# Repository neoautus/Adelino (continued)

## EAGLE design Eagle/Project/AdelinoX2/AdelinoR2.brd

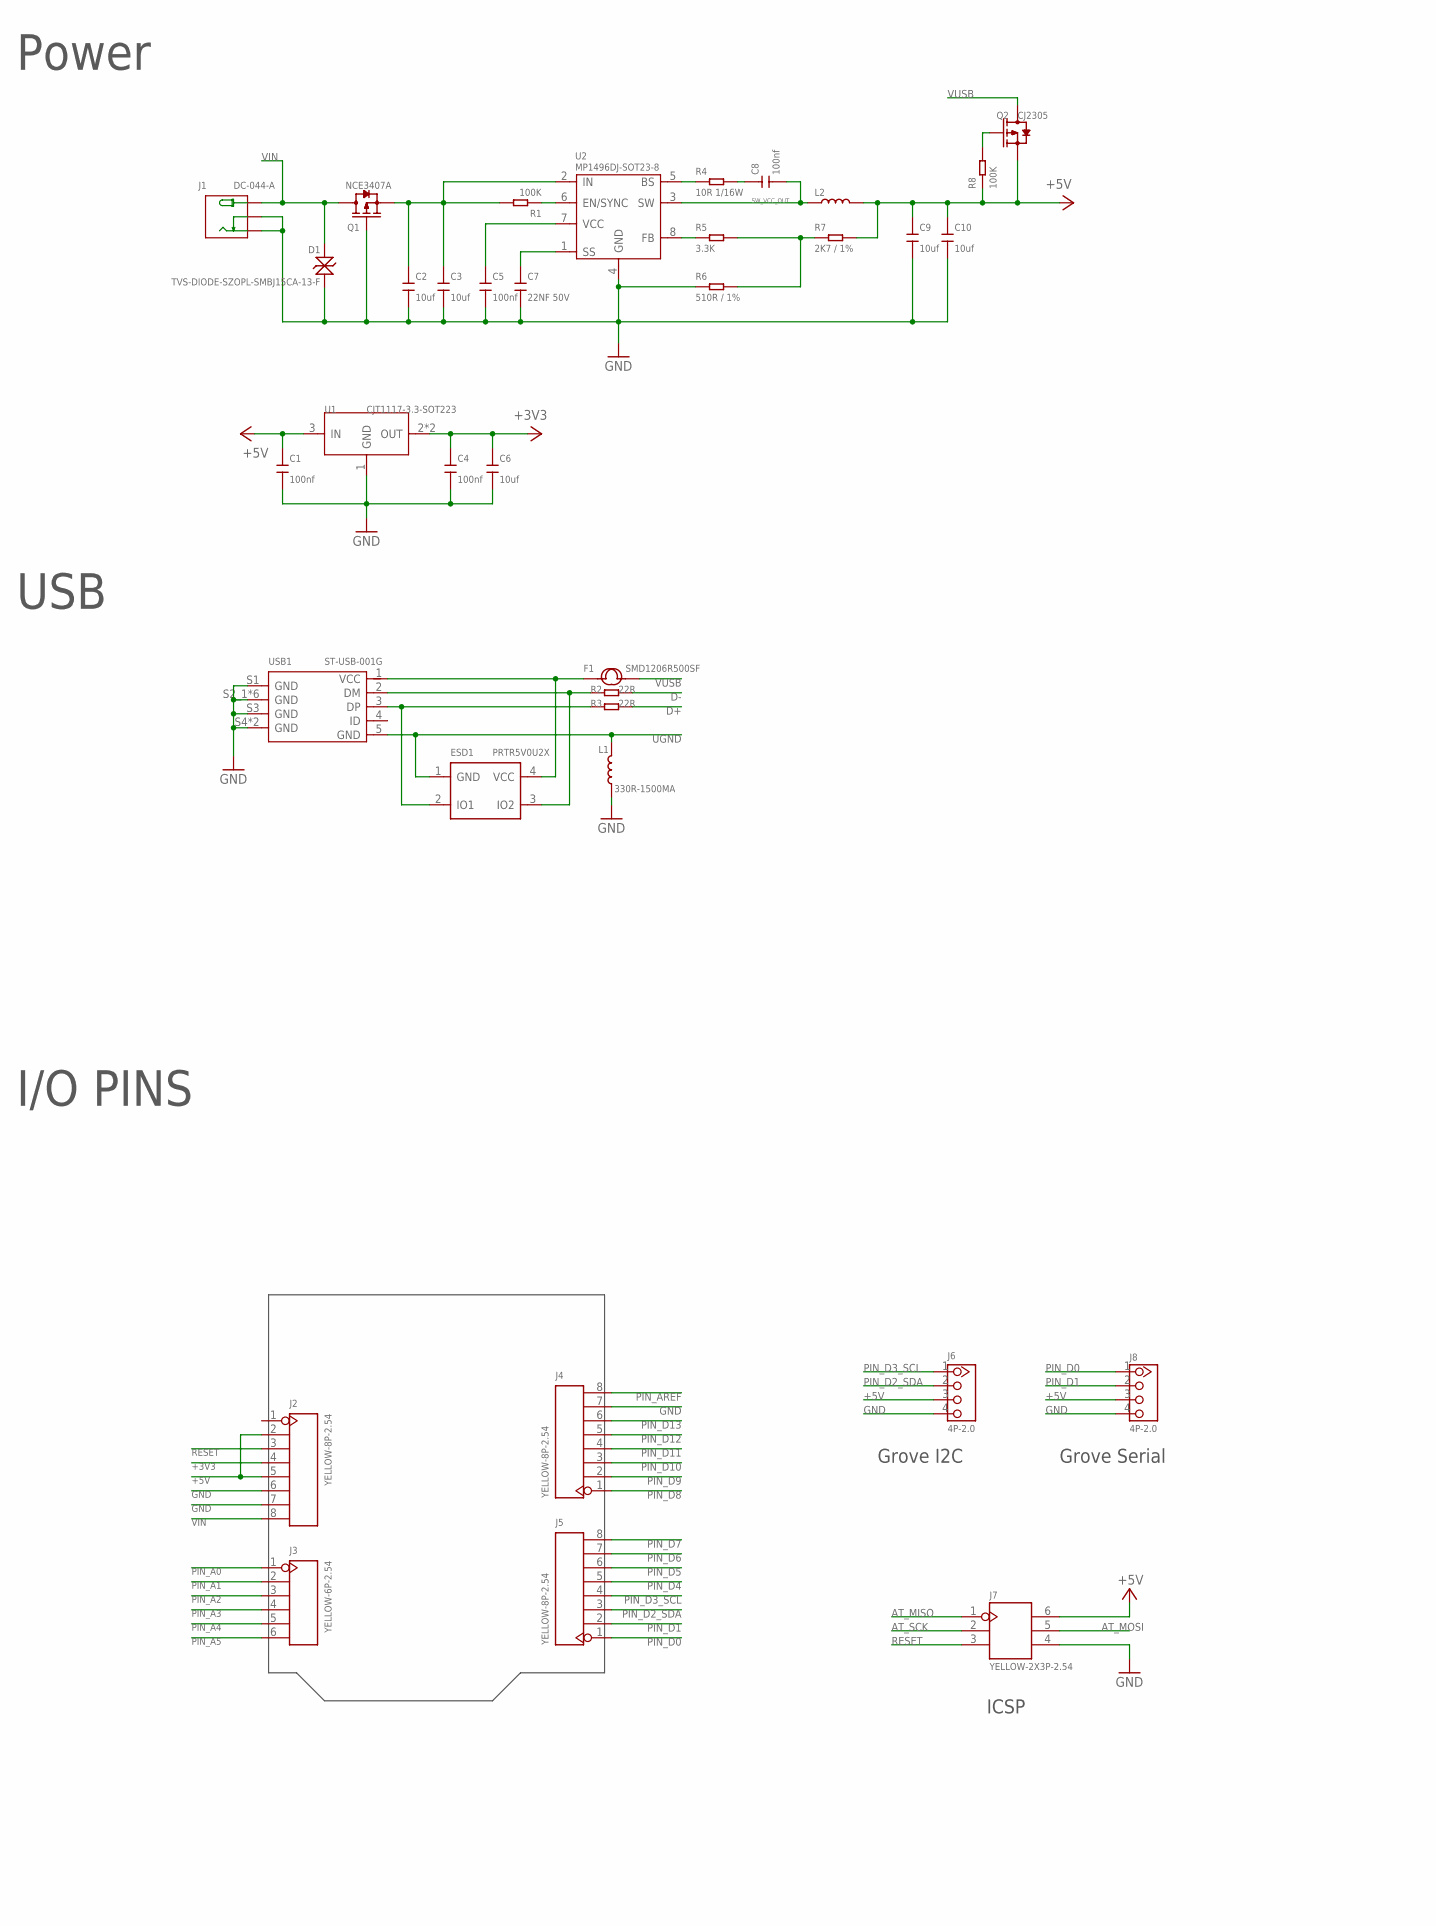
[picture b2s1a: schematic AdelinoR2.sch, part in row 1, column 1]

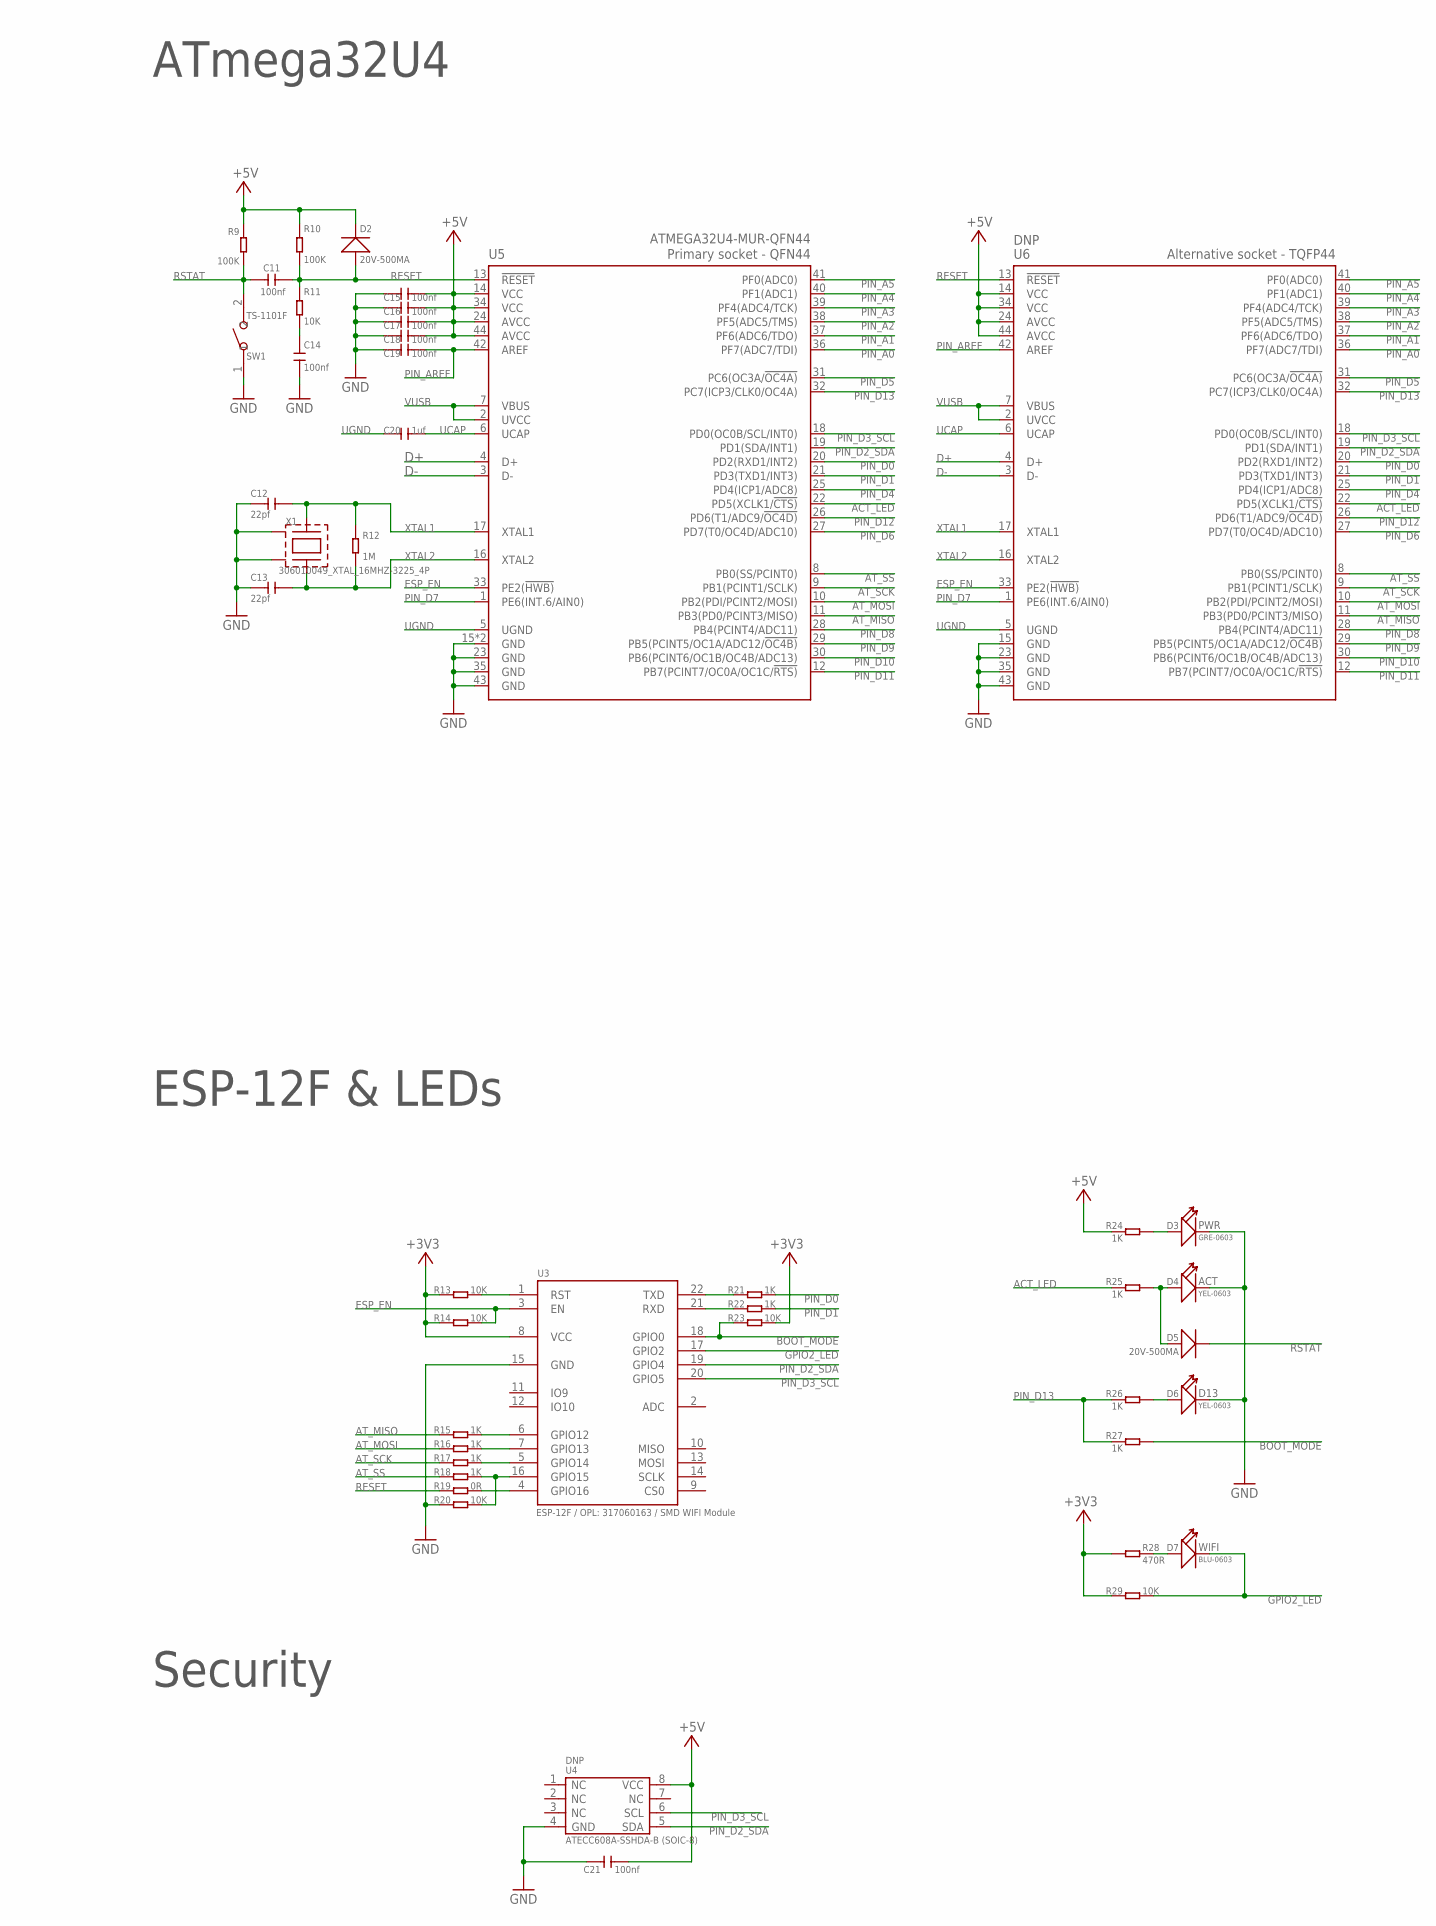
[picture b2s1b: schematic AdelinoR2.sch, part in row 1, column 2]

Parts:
C1, C4, C5, C8, C11, C14, C15, C16, C17, C18, C19, C21: 100nf; C0402
C2, C3, C6, C9, C10: 10uf; C0805
C7: 22NF 50V; C0402
C12, C13: 22pf; C0402
C20: 1uf; C0805
D1: TVS-DIODE-SZOPL-SMBJ15CA-13-F; DO-214AA
D2, D5: 20V-500MA; SOD-123
D3: GRE-0603; LED-0603
D4, D6: YEL-0603; LED-0603
D7: BLU-0603; LED-0603
ESD1: PRTR5V0U2X; SOT-143B
F1: SMD1206R500SF; F1206
J1: DC-044-A; DCJ3P-11.6X9.6X7.0MM
J2, J4, J5: YELLOW-8P-2.54; H8-2.54
J3: YELLOW-6P-2.54; H6-2.54
J6, J8: 4P-2.0; HW4-2.0
J7: YELLOW-2X3P-2.54; H2X3-2.54
L1: 330R-1500MA; L0805
L2: 10UH-225MA; L5040S
Q1: NCE3407A; SOT-23
Q2: CJ2305; SOT-23
R1, R8, R9, R10: 100K; R0402
R2, R3: 22R; R0402
R4: 10R 1/16W; R0402
R5: 3.3K; R0402
R6: 3K / 1%; R0603
R7: 2K7 / 1%; R0603
R11, R13, R14, R20, R23, R29: 10K; R0402
R12: 1M; R0402
R15, R16, R17, R18, R21, R22, R24, R25, R26, R27: 1K; R0402
R19: 0R; R0402
R28: 470R; R0402
SW1: TS-1101F; SW2-5.0-6.0X3.0X4.3MM
U1: CJT1117-3.3-SOT223; SOT-223
U2: MP1496DJ-SOT23-8; SOT-23-8
U3: ESP-12F / OPL: 317060163 / SMD WIFI Module; ESP-12F
U4: DNP; SOIC8-1.27-5X4MM; MPN ATECC608A-SSHDA-B
U5: ATMEGA32U4-MUR-QFN44; QFN44G-0.5-7X7MM
U6: DNP; TQFP44-0.8-9.6X9.6MM
USB1: ST-USB-001G; MICRO-USB5+4P-SMD-0.65-B
X1: 306010049_XTAL_16MHZ-3225_4P; X3225_4P

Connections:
+3V3: C4.2, C6.2, J2.4, R13.1, R14.1, R23.2, R28.1, R29.1, U1.2 (OUT), U1.TER (OUT), U3.8 (VCC)
+5V: C1.2, C9.2, C10.2, C15.1, C16.1, C17.1, C18.1, C21.1, D2.-, J2.2, J2.5, J6.3, J7.6, J8.3, L2.2, Q2.2 (S), R7.2, R8.1, R9.1, R10.2, R24.1, U1.3 (IN), U4.8 (VCC), U5.14 (VCC), U5.24 (AVCC), U5.34 (VCC), U5.44 (AVCC), U6.14 (VCC), U6.24 (AVCC), U6.34 (VCC), U6.44 (AVCC)
ACT_LED: R25.1, U5.22 (PD5(XCLK1/!CTS)), U6.22 (PD5(XCLK1/!CTS))
AT_MISO: J7.1, R15.1, U5.11 (PB3(PD0/PCINT3/MISO)), U6.11 (PB3(PD0/PCINT3/MISO))
AT_MOSI: J7.5, R16.1, U5.10 (PB2(PDI/PCINT2/MOSI)), U6.10 (PB2(PDI/PCINT2/MOSI))
AT_SCK: J7.2, R17.1, U5.9 (PB1(PCINT1/SCLK)), U6.9 (PB1(PCINT1/SCLK))
AT_SS: R18.1, U5.8 (PB0(SS/PCINT0)), U6.8 (PB0(SS/PCINT0))
BOOT_MODE: R23.1, R27.2, U3.18 (GPIO0)
D+: R3.2, U5.4 (D+), U6.4 (D+)
D-: R2.2, U5.3 (D-), U6.3 (D-)
ESP_EN: R14.2, U3.3 (EN), U5.33 (PE2(!HWB)), U6.33 (PE2(!HWB))
GND: C1.1, C2.1, C3.1, C4.1, C5.1, C6.1, C7.1, C9.1, C10.1, C12.1, C13.1, C14.2, C15.2, C16.2, C17.2, C18.2, C19.2, C21.2, D1.+, D3.-, D4.-, D6.-, J1.CDN1 (CDN), J1.CDN2 (CDN), J1.CDN3 (CDN), J1.CDN4 (CDN), J1.GND1 (-), J1.GND2 (-), J1.GND3 (-), J1.GND4 (-), J2.6, J2.7, J4.7, J6.4, J7.4, J8.4, L1.1, Q1.1 (G), R6.1, R20.1, SW1.1, U1.1 (GND), U2.4 (GND), U3.15 (GND), U4.4 (GND), U5.15 (GND), U5.23 (GND), U5.35 (GND), U5.43 (GND), U5.TAB (GND), U6.15 (GND), U6.23 (GND), U6.35 (GND), U6.43 (GND), USB1.S1 (GND), USB1.S2_1 (GND), USB1.S2_2 (GND), USB1.S2_3 (GND), USB1.S3 (GND), USB1.S4 (GND), USB1.S5_1 (GND), USB1.S5_2 (GND), USB1.S5_3 (GND), USB1.S6 (GND), X1.P$2 (GND1), X1.P$4 (GND2)
GPIO2_LED: D7.-, R29.2, U3.17 (GPIO2)
unnamed: ESD1.3 (IO2), R2.1, USB1.2 (DM)
unnamed: ESD1.2 (IO1), R3.1, USB1.3 (DP)
unnamed: Q2.1 (G), R8.2
unnamed: D7.+, R28.2
unnamed: R19.2, U3.4 (GPIO16)
unnamed: ESD1.4 (VCC), F1.1, USB1.1 (VCC)
unnamed: R15.2, U3.6 (GPIO12)
unnamed: C14.1, R11.2
unnamed: R16.2, U3.7 (GPIO13)
unnamed: C8.2, R4.2
unnamed: R21.1, U3.22 (TXD)
unnamed: R22.1, U3.21 (RXD)
unnamed: R17.2, U3.5 (GPIO14)
unnamed: R18.2, R20.2, U3.16 (GPIO15)
unnamed: R13.2, U3.1 (RST)
unnamed: R5.2, R6.2, R7.1
PIN_A0: J3.1, U5.36 (PF7(ADC7/TDI)), U6.36 (PF7(ADC7/TDI))
PIN_A1: J3.2, U5.37 (PF6(ADC6/TDO)), U6.37 (PF6(ADC6/TDO))
PIN_A2: J3.3, U5.38 (PF5(ADC5/TMS)), U6.38 (PF5(ADC5/TMS))
PIN_A3: J3.4, U5.39 (PF4(ADC4/TCK)), U6.39 (PF4(ADC4/TCK))
PIN_A4: J3.5, U5.40 (PF1(ADC1)), U6.40 (PF1(ADC1))
PIN_A5: J3.6, U5.41 (PF0(ADC0)), U6.41 (PF0(ADC0))
PIN_AREF: C19.1, J4.8, U5.42 (AREF), U6.42 (AREF)
PIN_D0: J5.1, J8.1, R21.2, U5.20 (PD2(RXD1/INT2)), U6.20 (PD2(RXD1/INT2))
PIN_D1: J5.2, J8.2, R22.2, U5.21 (PD3(TXD1/INT3)), U6.21 (PD3(TXD1/INT3))
PIN_D2_SDA: J5.3, J6.2, U3.19 (GPIO4), U4.5 (SDA), U5.19 (PD1(SDA/INT1)), U6.19 (PD1(SDA/INT1))
PIN_D3_SCL: J5.4, J6.1, U3.20 (GPIO5), U4.6 (SCL), U5.18 (PD0(OC0B/SCL/INT0)), U6.18 (PD0(OC0B/SCL/INT0))
PIN_D4: J5.5, U5.25 (PD4(ICP1/ADC8)), U6.25 (PD4(ICP1/ADC8))
PIN_D5: J5.6, U5.31 (PC6(OC3A/!OC4A)), U6.31 (PC6(OC3A/!OC4A))
PIN_D6: J5.7, U5.27 (PD7(T0/OC4D/ADC10)), U6.27 (PD7(T0/OC4D/ADC10))
PIN_D7: J5.8, U5.1 (PE6(INT.6/AIN0)), U6.1 (PE6(INT.6/AIN0))
PIN_D8: J4.1, U5.28 (PB4(PCINT4/ADC11)), U6.28 (PB4(PCINT4/ADC11))
PIN_D9: J4.2, U5.29 (PB5(PCINT5/OC1A/ADC12/!OC4B)), U6.29 (PB5(PCINT5/OC1A/ADC12/!OC4B))
PIN_D10: J4.3, U5.30 (PB6(PCINT6/OC1B/OC4B/ADC13)), U6.30 (PB6(PCINT6/OC1B/OC4B/ADC13))
PIN_D11: J4.4, U5.12 (PB7(PCINT7/OC0A/OC1C/!RTS)), U6.12 (PB7(PCINT7/OC0A/OC1C/!RTS))
PIN_D12: J4.5, U5.26 (PD6(T1/ADC9/!OC4D)), U6.26 (PD6(T1/ADC9/!OC4D))
PIN_D13: J4.6, R26.1, R27.1, U5.32 (PC7(ICP3/CLK0/OC4A)), U6.32 (PC7(ICP3/CLK0/OC4A))
RESET: C11.1, D2.+, J2.3, J7.3, R10.1, R11.1, R19.1, U5.13 (!RESET), U6.13 (!RESET)
RSTAT: C11.2, D5.-, R9.2, SW1.2
SW_BS: R4.1, U2.5 (BS)
SW_EN: R1.1, U2.6 (EN/SYNC)
SW_FB: R5.1, U2.8 (FB)
SW_SS: C7.2, U2.1 (SS)
SW_VCAP: C5.2, U2.7 (VCC)
SW_VCC_IN: C2.2, C3.2, Q1.2 (S), R1.2, U2.2 (IN)
SW_VCC_OUT: C8.1, L2.1, U2.3 (SW)
UCAP: C20.2, U5.6 (UCAP), U6.6 (UCAP)
UGND: C20.1, ESD1.1 (GND), L1.2, U5.5 (UGND), U6.5 (UGND), USB1.5 (GND)
VIN: D1.-, J1.VCC1 (+), J1.VCC2 (+), J1.VCC3 (+), J1.VCC4 (+), J2.8, Q1.3 (D)
VUSB: F1.2, Q2.3 (D), U5.2 (UVCC), U5.7 (VBUS), U6.2 (UVCC), U6.7 (VBUS)
XTAL1: C12.2, R12.2, U5.17 (XTAL1), U6.17 (XTAL1), X1.P$1
XTAL2: C13.2, R12.1, U5.16 (XTAL2), U6.16 (XTAL2), X1.P$3
_ACT: D4.+, D5.+, R25.2
_D13: D6.+, R26.2
_PWR: D3.+, R24.2

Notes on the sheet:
USB
Power
ATmega32U4
ESP-12F & LEDs
I/O PINS
Grove I2C
Grove Serial
Security
ICSP

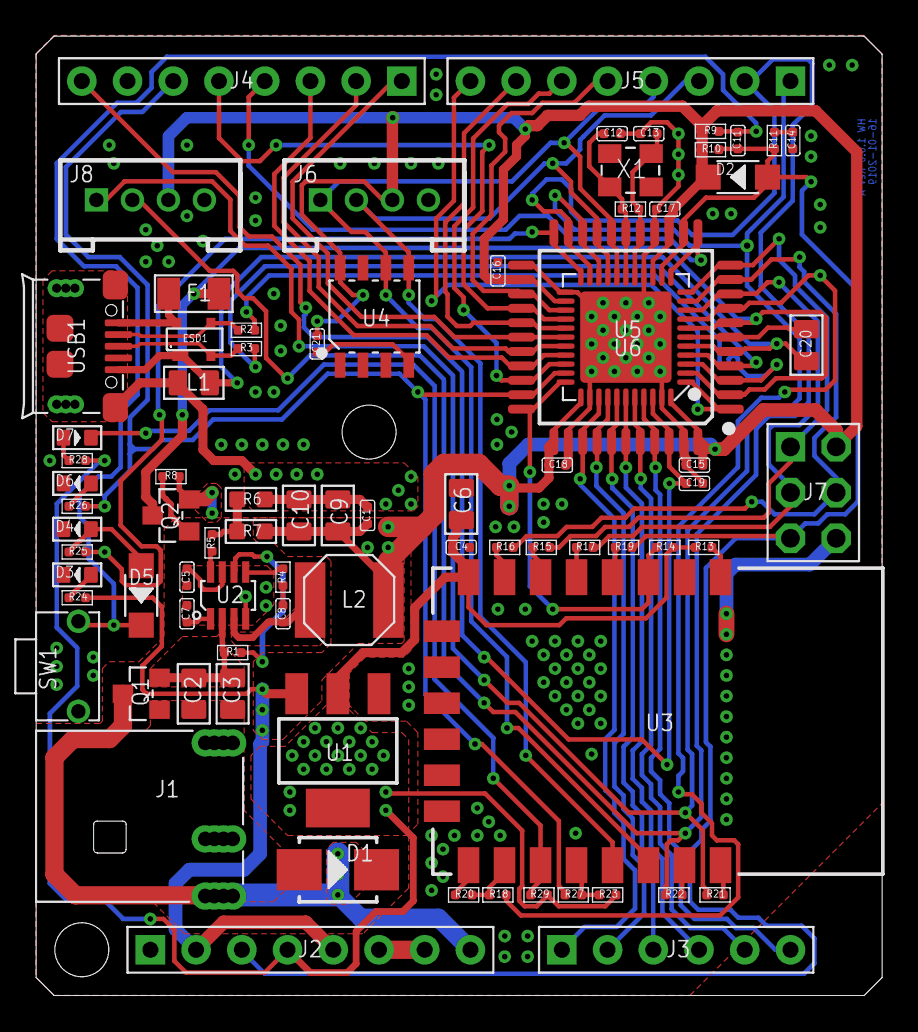
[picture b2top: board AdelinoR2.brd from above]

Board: 2 copper layers, 47.0 x 53.3 mm, 80 parts (0 on the bottom side), 68 nets.

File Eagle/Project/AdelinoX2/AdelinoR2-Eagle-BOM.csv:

"Parts";"Qty";"Value";"Device";"Package";"OPL";"MPN";"DESC"
"R19";1;"0R";"SMD-RES-0R-5%-1/16W(0402)";"R0402";301010000;"RC0402JR-070RL";"0R"
"R1, R8, R9, R10";4;"100K";"SMD-RES-100K-1%-1/16W(0402)";"R0402";301010456;"RC0402FR-07100KL";"100K"
"C1, C4, C5, C8, C11, C14, C15, C16, C17, C18, C19, C21";12;"100nf";"CERAMIC-100NF-25V-10%-X7R(0402)";"C0402";302010024;"CC0402KRX7R8BB104";"100nf"
"R11, R13, R14, R20, R23, R29";6;"10K";"SMD-RES-10K-1%-1/16W(0402)";"R0402";301010047;"RC0402FR-0710KL";"10K 1/16W"
"R4";1;"10R 1/16W";"SMD-RES-10R-1%-1/16W(0402)";"R0402";301010444;"RC0402FR-0710RL";"10R 1/16W"
"L2";1;"10UH-225MA";"SMD-INDUCTOR-10UH-20%-2.35A(2P-5X5X4MM)";"L5040S";303010147;;"SMD-INDUCTOR-10UH-20%-2.35A(2P-5X5X4MM)"
"C2, C3, C6, C9, C10";5;"10uf";"CERAMIC-10UF-25V-10%-X5R(0805)";"C0805";302010178;"CC0805KKX5R8BB106";"10uf"
"R15, R16, R17, R18, R21, R22, R24, R25, R26, R27";10;"1K";"SMD-RES-1K-5%-1/16W(0402)";"R0402";301010006;"RC0402JR-071KL";"1K"
"R12";1;"1M";"SMD-RES-1M-1%-1/16W(0402)";"R0402";301010043;"RC0402FR-071ML";"1M"
"C20";1;"1uf";"CERAMIC-1UF-25V-10%-X7R(0805)";"C0805";302010179;"CC0805KKX7R8BB105";"1uf"
"D2, D5";2;"20V-500MA";"SMD-DIODE-SCHOTTKY-20V-500MA(SOD-123)P";"SOD-123";304020028;"MBR0520LT1G";"20V-500MA"
"C7";1;"22NF 50V";"CERAMIC-22NF-50V-10%-X7R(0402)";"C0402";302010242;"CC0402KRX7R9BB223";"22NF 50V"
"R2, R3";2;"22R";"SMD-RES-22R-1%-1/16W(0402)";"R0402";301010052;"RC0402FR-0722RL";"22R"
"C12, C13";2;"22pf";"CERAMIC-22PF-50V-5%-NPO(0402)";"C0402";302010018;"CC0402JRNPO9BN220";"22pf"
"R7";1;"2K7 / 1%";"SMD-RES-2.7K-1%-1/10W(0603)";"R0603";301010193;;"2K7 / 1%"
"R5";1;"3.3K";"SMD-RES-3.3K-5%-1/16W(0402)";"R0402";301010035;"RC0402JR-073K3L";"3.3K"
"X1";1;"306010049_XTAL_16MHZ-3225_4P";"306010049_XTAL_16MHZ-3225_4P";"X3225_4P";;;"SMD Crystal 16MHz-9pF-10ppm-40R;4P-L3.2*W2.5mm, SKU: 306010049"
"L1";1;"330R-1500MA";"SMD-FERRITE-BEAD-330R-1500MA(0805)'0805'";"L0805";303030006;"BLM21PG331SN1D";"330R-1500MA"
"R6";1;"3K / 1%";"SMD-RES-510R-1%-1/10W(0603)";"R0603";301010215;;"510R / 1%"
"R28";1;"470R";"SMD-RES-470R-5%-1/16W(0402)";"R0402";301010013;"RC0402JR-07470RL";"470R 1/16W"
"J6, J8";2;"4P-2.0";"GROVE-CONNECTOR-DIP(4P-2.0)";"HW4-2.0";320110033;;"4P-2.0"
"U5";1;"ATMEGA32U4-MUR-QFN44";"MCU-ATMEGA32U4-MUR(VQFN44)";"QFN44G-0.5-7X7MM";310010016;"ATMEGA32U4-MUR";"ATMEGA32U4-MUR-QFN44"
"D7";1;"BLU-0603";"SMD-LED-CLEAR-BLUE(0603)";"LED-0603";304090045;"19-217-BHC-ZL1M2RY-3T";"BLUE-0603"
"Q2";1;"CJ2305";"SMD-MOSFET-P-CH-8V-4.1A-CJ2305(SOT-23)";"SOT-23";305030014;"CJ2305";"CJ2305"
"U1";1;"CJT1117-3.3-SOT223";"PMIC-CJT1117-3.3(SOT223)";"SOT-223";310030097;"CJT1117-3.3";"CJT1117-3.3-SOT223"
"J1";1;"DC-044-A";"JACK-DC-044-A";"DCJ3P-11.6X9.6X7.0MM";320120002;"JACK-DC-044-A";"DC-044-A"
"U4";1;"DNP";"ATECC608(SOIC8)";"SOIC8-1.27-5X4MM";"ATECC608A-SSHDA-B (SOIC-8)";"ATECC608A-SSHDA-B";"ATECC608ASSHDAB-SOIC8"
"U6";1;"DNP";"MCU-ATMEGA32U4-AU(TQFP44)";"TQFP44-0.8-9.6X9.6MM";310010010;"ATMEGA32U4";"ATMEGA32U4-TQFP44"
"U3";1;"ESP-12F / OPL: 317060163 / SMD WIFI Module";"ESP-12F";"ESP-12F";317060163;;"ESP-12F / OPL: 317060163 / SMD WIFI Module"
"D3";1;"GRE-0603";"SMD-LED-CLEAR-GREEN(0603)";"LED-0603";304090043;"19-217-G7C-AN1P2-3T";"GREEN-0603"
"U2";1;"MP1496DJ-SOT23-8";"PMIC-MP1496DJ(SOT23-8)";"SOT-23-8";310030121;"MP1496DJ";"MP1496DJ-SOT23-8"
"Q1";1;"NCE3407A";"SMD-MOSFET-P-CH-VDC=30V-ID=4.3A-NCE3407A(SOT-23)";"SOT-23";305030010;"NCE3407A";"NCE3407A"
"ESD1";1;"PRTR5V0U2X";"SMD-DIODE-TVS-5.5V";"SOT-143B";304050022;"NXP";"PRTR5V0U2X"
"D1";1;"SMBJ15CA-13-F";"SMBJ15CA-13-F";"DO-214AA";"SMBJ15CA-13-F";"SMBJ15CA-13-F";"SMD TVS DIODE 15VWM 24.4VC SMA;DO-214AA(SMB)"
"F1";1;"SMD1206R500SF";"SMD-PPTC-500MA(1206)";"F1206";307010002;"SMD1206R500SF";"SMD1206R500SF"
"USB1";1;"ST-USB-001G";"MICRO-USB-SMD-B-WITHOUT-POST-W/P(ST-USB-001G)";"MICRO-USB5+4P-SMD-0.65-B";320010000;"ST-USB-001G";"ST-USB-001G"
"SW1";1;"TS-1101F";"DIP-BUTTON(2P-6.0X3.0X4.3MM)-TS-1101F";"SW2-5.0-6.0X3.0X4.3MM";311020025;"TS-1101F";"TS-1101F"
"D4";1;"YEL-0603";"SMD-LED-CLEAR-YELLOW(0603)";"LED-0603";304090044;"19-217-Y5C-AM1N1VY-3T";"YELLOW-0603"
"D6";1;"YEL-0603";"SMD-LED-CLEAR-YELLOW(0603)";"LED-0603";304090044;"19-217-Y5C-AM1N1VY-3T";"YELLOW-0603"
"J7";1;"YELLOW-2X3P-2.54";"DIP-YELLOW-MALE-HEADER-VERT(2X3P-2.54)";"H2X3-2.54";320020027;"P125-1203A0BS116A2";"YELLOW-2X3P-2.54"
"J3";1;"YELLOW-6P-2.54";"DIP-YELLOW-FEMALE-HEADER-VERT(6P-2.54)";"H6-2.54";320030019;"F185-1106A1BSYA3";"YELLOW-6P-2.54"
"J2, J4, J5";3;"YELLOW-8P-2.54";"DIP-YELLOW-FEMALE-HEADER(8P-2.54)";"H8-2.54";320030065;"F185-1108A1BSYC1";"YELLOW-8P-2.54"

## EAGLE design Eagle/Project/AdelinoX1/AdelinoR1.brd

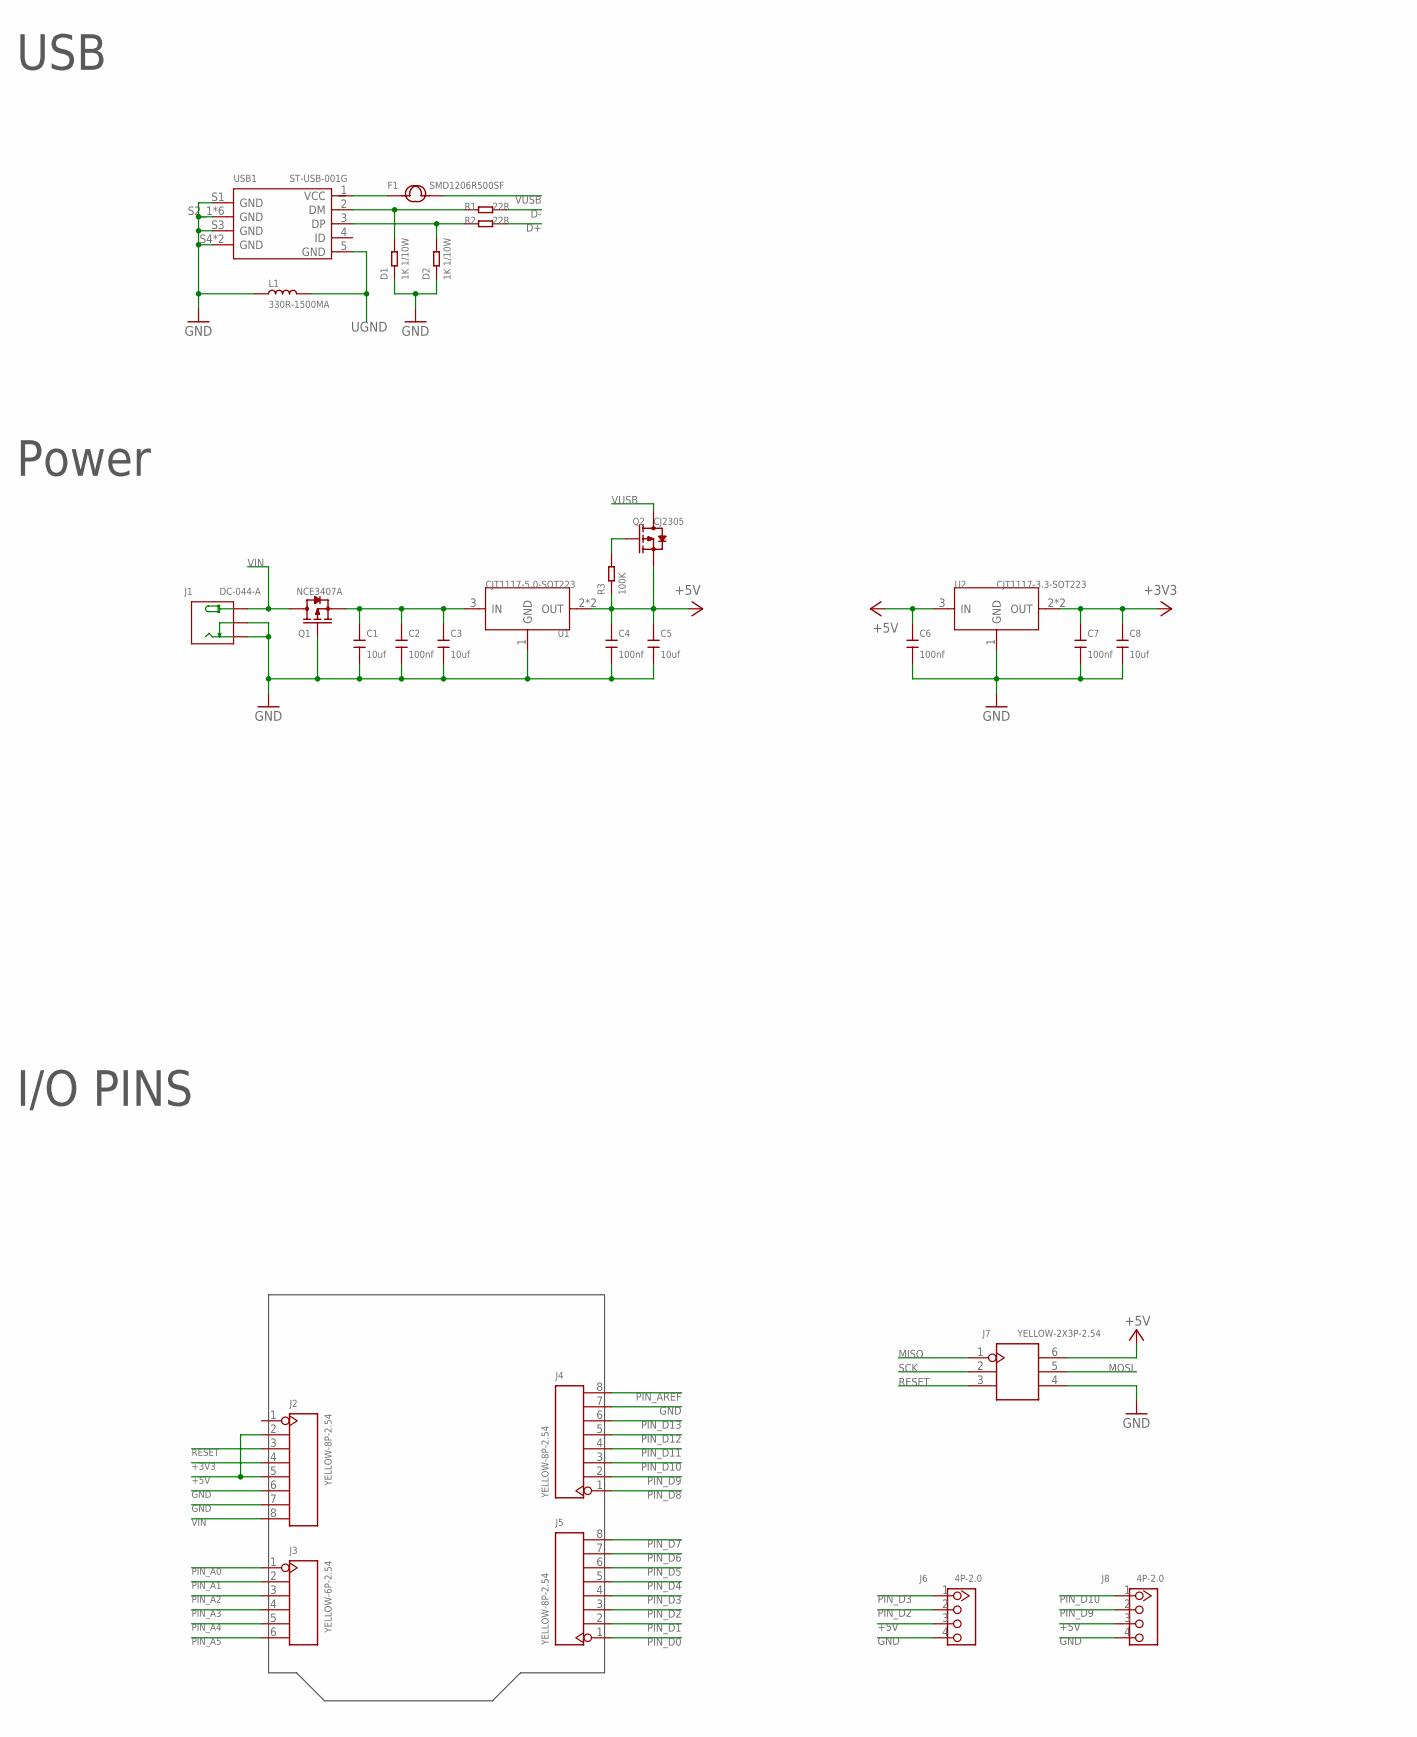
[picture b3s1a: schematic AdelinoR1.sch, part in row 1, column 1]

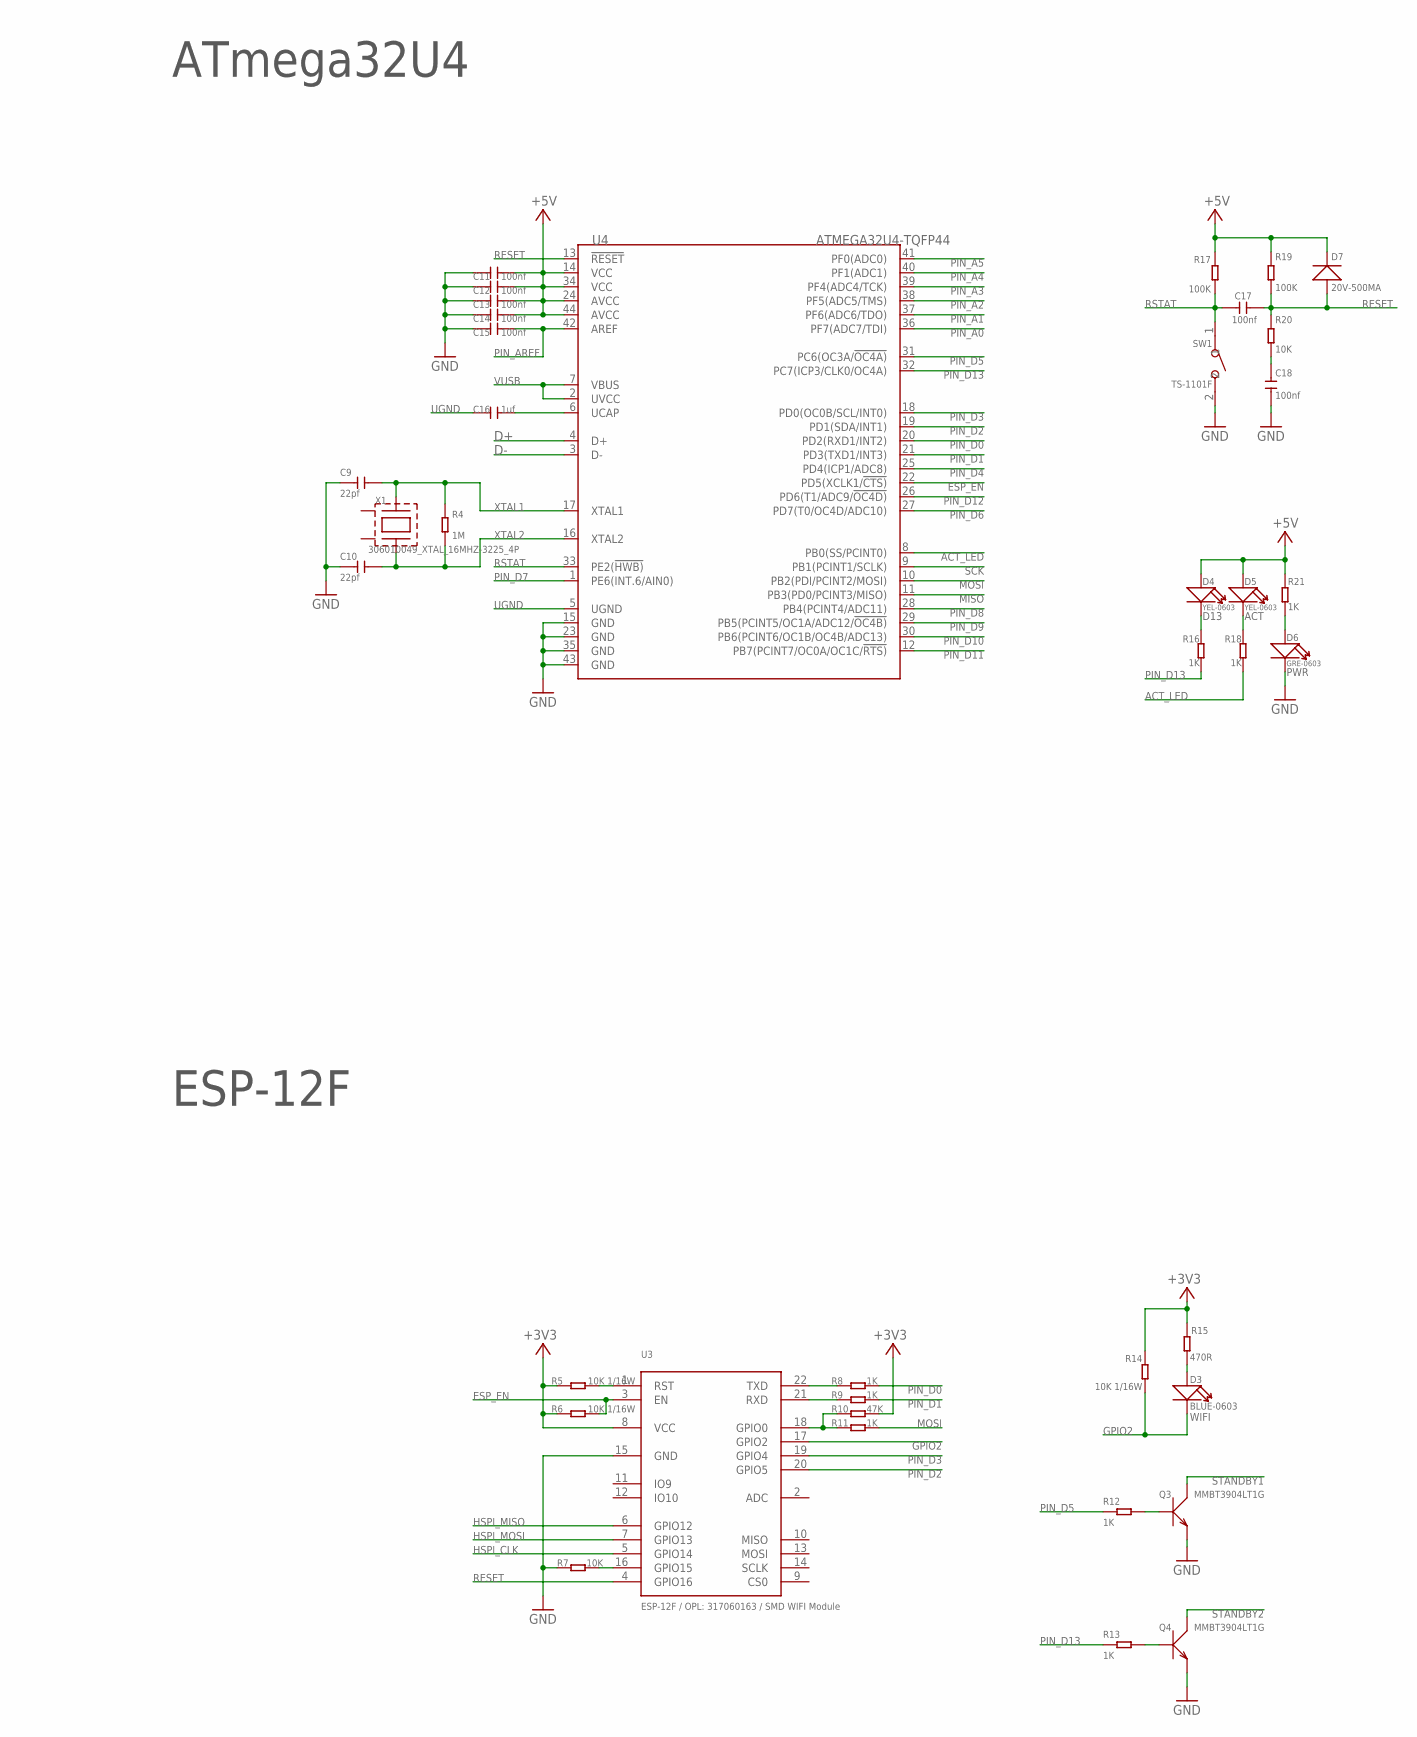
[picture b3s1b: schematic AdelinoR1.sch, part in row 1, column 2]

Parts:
C1, C3, C5, C8: 10uf; C0805
C2, C4, C6, C7, C11, C12, C13, C14, C15, C17, C18: 100nf; C0402
C9, C10: 22pf; C0402
C16: 1uf; C0805
D1, D2: 1K 1/10W; D0603
D3: BLUE-0603; LED-0603
D4, D5: YEL-0603; LED-0603
D6: GRE-0603; LED-0603
D7: 20V-500MA; SOD-123
F1: SMD1206R500SF; F1206
J1: DC-044-A; DCJ3P-11.6X9.6X7.0MM
J2, J4, J5: YELLOW-8P-2.54; H8-2.54
J3: YELLOW-6P-2.54; H6-2.54
J6, J8: 4P-2.0; HW4-2.0
J7: YELLOW-2X3P-2.54; H2X3-2.54
L1: 330R-1500MA; L0805
Q1: NCE3407A; SOT-23
Q2: CJ2305; SOT-23
Q3, Q4: MMBT3904LT1G; SOT-23
R1, R2: 22R; R0402
R3, R17, R19: 100K; R0402
R4: 1M; R0402
R5, R6, R14: 10K 1/16W; R0402
R7, R20: 10K; R0402
R8, R9, R11, R12, R13, R16, R18, R21: 1K; R0402
R10: 47K; R0402
R15: 470R; R0402
SW1: TS-1101F; SW2-5.0-6.0X3.0X4.3MM
U1: CJT1117-5.0-SOT223; SOT-223
U2: CJT1117-3.3-SOT223; SOT-223
U3: ESP-12F / OPL: 317060163 / SMD WIFI Module; ESP-12F
U4: ATMEGA32U4-TQFP44; TQFP44-0.8-9.6X9.6MM
USB1: ST-USB-001G; MICRO-USB5+4P-SMD-0.65-B
X1: 306010049_XTAL_16MHZ-3225_4P; X3225_4P

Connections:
+3V3: C7.2, C8.2, J2.4, R5.1, R6.1, R10.2, R14.2, R15.2, U2.2 (OUT), U2.TER (OUT), U3.8 (VCC)
+5V: C4.2, C5.2, C6.2, C11.1, C12.1, C13.1, C14.1, D4.+, D5.+, D7.-, J2.2, J2.5, J6.3, J7.6, J8.3, Q2.2 (S), R3.1, R17.1, R19.2, R21.1, U1.2 (OUT), U1.TER (OUT), U2.3 (IN), U4.14 (VCC), U4.24 (AVCC), U4.34 (VCC), U4.44 (AVCC)
ACT_LED: R18.2, U4.8 (PB0(SS/PCINT0))
D+: R2.2, U4.4 (D+)
D-: R1.2, U4.3 (D-)
ESP_EN: R6.2, U3.3 (EN), U4.22 (PD5(XCLK1/!CTS))
GND: C1.1, C2.1, C3.1, C4.1, C5.1, C6.1, C7.1, C8.1, C9.1, C10.1, C11.2, C12.2, C13.2, C14.2, C15.2, C18.2, D1.1, D2.1, D6.-, J1.CDN1 (CDN), J1.CDN2 (CDN), J1.CDN3 (CDN), J1.CDN4 (CDN), J1.GND1 (-), J1.GND2 (-), J1.GND3 (-), J1.GND4 (-), J2.6, J2.7, J4.7, J6.4, J7.4, J8.4, L1.1, Q1.1 (G), Q3.2 (E), Q4.2 (E), R7.1, SW1.2, U1.1 (GND), U2.1 (GND), U3.15 (GND), U4.15 (GND), U4.23 (GND), U4.35 (GND), U4.43 (GND), USB1.S1 (GND), USB1.S2_1 (GND), USB1.S2_2 (GND), USB1.S2_3 (GND), USB1.S3 (GND), USB1.S4 (GND), USB1.S5_1 (GND), USB1.S5_2 (GND), USB1.S5_3 (GND), USB1.S6 (GND)
GND1: X1.P$2 (GND1)
GND2: X1.P$4 (GND2)
GPIO0: R10.1, R11.1, U3.18 (GPIO0)
GPIO2: D3.-, R14.1, U3.17 (GPIO2)
HSPI_CLK: U3.5 (GPIO14)
HSPI_MISO: U3.6 (GPIO12)
HSPI_MOSI: U3.7 (GPIO13)
MISO: J7.1, U4.11 (PB3(PD0/PCINT3/MISO))
MOSI: J7.5, R11.2, U4.10 (PB2(PDI/PCINT2/MOSI))
unnamed: D1.2, R1.1, USB1.2 (DM)
unnamed: D2.2, R2.1, USB1.3 (DP)
unnamed: Q2.1 (G), R3.2
unnamed: R7.2, U3.16 (GPIO15)
unnamed: D6.+, R21.2
unnamed: D5.-, R18.1
unnamed: C16.2, U4.6 (UCAP)
unnamed: D4.-, R16.1
unnamed: F1.1, USB1.1 (VCC)
unnamed: C1.2, C2.2, C3.2, Q1.2 (S), U1.3 (IN)
unnamed: D3.+, R15.1
unnamed: C18.1, R20.2
unnamed: R5.2, U3.1 (RST)
unnamed: Q3.1 (B), R12.2
unnamed: R8.1, U3.22 (TXD)
unnamed: R9.1, U3.21 (RXD)
unnamed: Q4.1 (B), R13.2
PIN_A0: J3.1, U4.36 (PF7(ADC7/TDI))
PIN_A1: J3.2, U4.37 (PF6(ADC6/TDO))
PIN_A2: J3.3, U4.38 (PF5(ADC5/TMS))
PIN_A3: J3.4, U4.39 (PF4(ADC4/TCK))
PIN_A4: J3.5, U4.40 (PF1(ADC1))
PIN_A5: J3.6, U4.41 (PF0(ADC0))
PIN_AREF: C15.1, J4.8, U4.42 (AREF)
PIN_D0: J5.1, R8.2, U4.20 (PD2(RXD1/INT2))
PIN_D1: J5.2, R9.2, U4.21 (PD3(TXD1/INT3))
PIN_D2: J5.3, J6.2, U3.20 (GPIO5), U4.19 (PD1(SDA/INT1))
PIN_D3: J5.4, J6.1, U3.19 (GPIO4), U4.18 (PD0(OC0B/SCL/INT0))
PIN_D4: J5.5, U4.25 (PD4(ICP1/ADC8))
PIN_D5: J5.6, R12.1, U4.31 (PC6(OC3A/!OC4A))
PIN_D6: J5.7, U4.27 (PD7(T0/OC4D/ADC10))
PIN_D7: J5.8, U4.1 (PE6(INT.6/AIN0))
PIN_D8: J4.1, U4.28 (PB4(PCINT4/ADC11))
PIN_D9: J4.2, J8.2, U4.29 (PB5(PCINT5/OC1A/ADC12/!OC4B))
PIN_D10: J4.3, J8.1, U4.30 (PB6(PCINT6/OC1B/OC4B/ADC13))
PIN_D11: J4.4, U4.12 (PB7(PCINT7/OC0A/OC1C/!RTS))
PIN_D12: J4.5, U4.26 (PD6(T1/ADC9/!OC4D))
PIN_D13: J4.6, R13.1, R16.2, U4.32 (PC7(ICP3/CLK0/OC4A))
RESET: C17.1, D7.+, J2.3, J7.3, R19.1, R20.1, U3.4 (GPIO16), U4.13 (!RESET)
RSTAT: C17.2, R17.2, SW1.1, U4.33 (PE2(!HWB))
SCK: J7.2, U4.9 (PB1(PCINT1/SCLK))
STANDBY1: Q3.3 (C)
STANDBY2: Q4.3 (C)
UGND: C16.1, L1.2, U4.5 (UGND), USB1.5 (GND)
VIN: J1.VCC1 (+), J1.VCC2 (+), J1.VCC3 (+), J1.VCC4 (+), J2.8, Q1.3 (D)
VUSB: F1.2, Q2.3 (D), U4.2 (UVCC), U4.7 (VBUS)
XTAL1: C9.2, R4.2, U4.17 (XTAL1), X1.P$1
XTAL2: C10.2, R4.1, U4.16 (XTAL2), X1.P$3

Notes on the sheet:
USB
Power
ATmega32U4
ESP-12F
I/O PINS

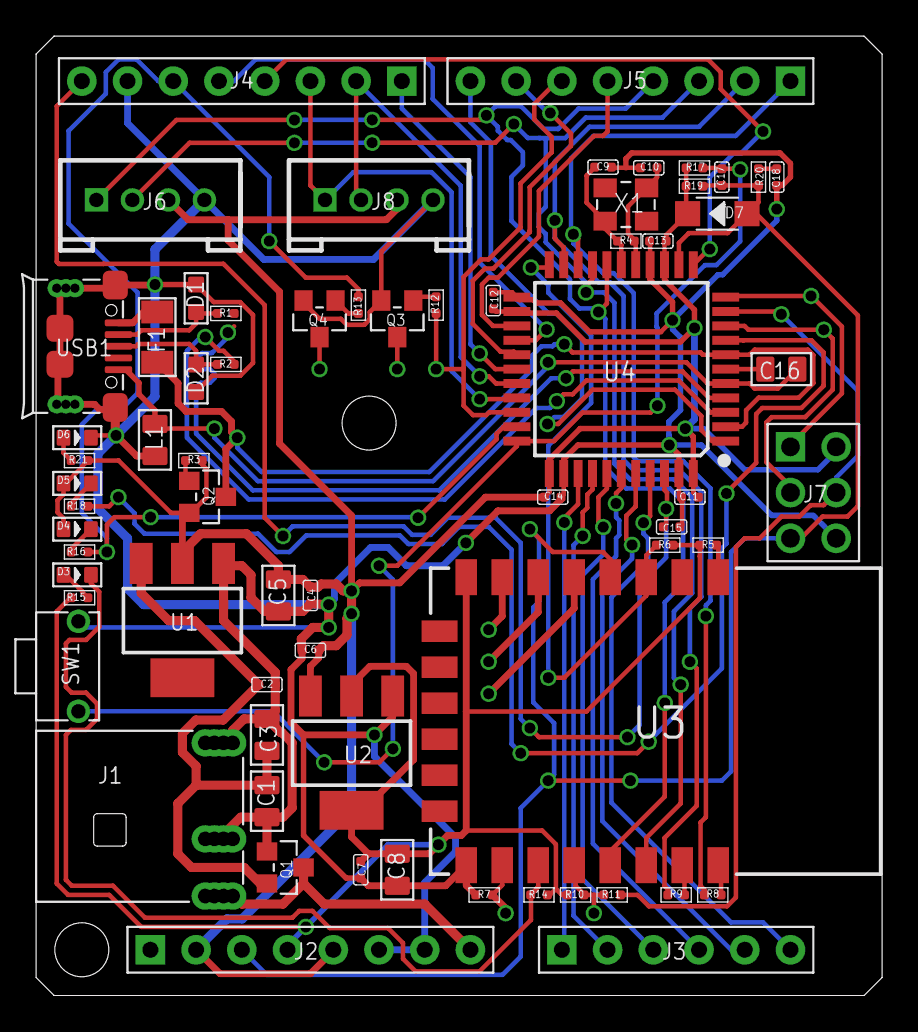
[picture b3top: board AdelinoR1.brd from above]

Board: 2 copper layers, 47.0 x 53.3 mm, 67 parts (0 on the bottom side), 57 nets.
